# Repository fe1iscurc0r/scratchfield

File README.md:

# scratchfield — 实验田

[中文](README.md) · [English](README_en.md)

> 连接即正义，控制即毁灭。
> 集成地狱不是事故，是特色。我们把别人的灵感拔下来，授粉进自己的土壤，长成自己的东西。
> 我们不套壳——每个组件都带融合报告，来源、许可、改动点、验收，白纸黑字。

**scratchfield**（实验田）——以**授粉（Pollination）**为方法论的集成工程展示面 + 插件商城。活跃开发在私有工作仓进行，本仓是公开展示面，按里程碑快照更新。**当前快照：2026-10-07。**

## 这是什么

一句话：**把上游好想法「授粉」进自家系统，长成自己的东西。**

授粉不是 fork 粘贴，是"拆解 → 改造 → 集成 → 留下报告"。每个授粉组件都登记来源、许可、改造点、验收结果，许可账本见 `github_haul/FUSION-LOG-2026-08-16.md` 与 [NOTICE（第三方版权声明全集）](NOTICE)。

### 自家核心资产（本仓展示的主菜）

- **工具总线**（`mcpserver/`）——MCP 适配层，统一注册 / 调度 / 鉴权。自研，含多领域工具封装与 agent-manifest 契约。
- **射频大脑**（`mcpserver/rf_brain/`）——协议无关的射频解调链。自研：OOK 解码器家族（Acurite/LaCrosse/PWM/PPM/Manchester）、DSP 滤波链、dcp 二进制帧、哨兵桥入库。
- **无线电套件 radio_suite**——FT8/WSPR/SSTV/NOAA APT 解码、SDR 频谱面板、APRS iGate、IC-705 CI-V 控制。独立组件走总线接入本体。
- **哨兵网格固件**（`firmware/`）——ESP32-S3 + SX1278 边缘频谱哨兵，433MHz 传感器信号从天线到记忆的完整链路。自研。
- **科研工作台**——ELN 实验记录、文献库、材料数据工具台（TGA/DSC/XRD）、材料性能预测管线；领域包机制（`domains/`）支撑多学科扩展。
- **授粉插件商城**（`plugins/`）——所有授粉改造过的组件统一登记，自由添加、即插即用。
- **记忆钩子**（`hooks/`）——事实索引 / 矛盾检出 / supersedes 边。自研。
- **NEKO 集成体**（`NEKO/`）——**旗舰授粉案例**：以 Apache-2.0 上游 NEKO 桌宠为身体层（Live2D/TTS/ASR/视觉），自研集成层（启动 wrapper、provider overlay、注入路由、灵魂桥）将其接入自家人格内核（记忆 / RAG / 决策）与 Hermes 生态。

### 近期亮点（2026-10 快照）

- **巨石治理收官**——agentserver 主入口 3096 行拆为 30 行薄入口 + 11 子模块；前端 SkillView/App/ForumSidebarRight 三大巨石组件分步拆解，App.vue 转向 composable 架构并附状态依赖图
- **Agent 安全防线**——5 篇前沿攻击论文（间接注入/技能组合失控/跨租户干扰）转化为威胁模型清单，工具总线新增风险等级注解与任务级调用链留痕
- **RF-Agent 频谱调度设计**——参考层级语言-Agent 频谱感知架构，为 IC-705/RTL-SDR 工作流设计三层调度（指令理解→任务规划→设备执行），设计稿先行
- **材料线对口授粉**——sparse AFM 跨尺度力学重建、纳米颗粒分散度过程链优化两篇方法论落地为调研笔记，直连木质素 NPs→水凝胶研究主线
- **授粉轮 35 期持续产出**——热分析动力学、EIS、糖链与聚合物拓扑、GNSS 定位安全等十轮方法论报告入库
- **配置收口与配置即文档**——apiserver 环境变量统一进 config.py + .env.example 全量补齐
- **一键体检**——`scripts/doctor.py` 应用层自检 + `doctor_env.py` 环境自检，装到哪一步坏了一眼可见

### 身份声明

- 本仓是**授粉实验田**，不是任何上游的套壳。底层引擎（NagaAgent、NEKO、llama.cpp 等 Apache/MIT 组件）只是技术栈的一部分，列于各组件致谢；自家产出是集成层、工具总线、射频/固件、授粉插件。
- 类比：Chrome 基于 Chromium，Firefox 基于 Gecko——引擎是引擎，品牌是品牌。我们卖的是"把上游消化成自己的"这个能力。
- 每个授粉条目的来源与许可边界见 FUSION-LOG 与各插件条目，法律与道义都讲得清。

## 授粉是什么

授粉 = 上游灵感 → 拆解 → 改造 → 集成。不是 fork 粘贴，而是把「能长进我们系统的那部分」移植进来，留下完整的授粉报告（来源 / 许可 / 改造点 / 验收）。许可账本见 `github_haul/FUSION-LOG-2026-08-16.md`。

## 目录

| 路径 | 内容 |
|------|------|
| `mcpserver/` | 工具总线（自研，含 rf_brain 射频大脑） |
| `apiserver/` | FastAPI 主后端（ELN/文献/数据工具/人格/记忆） |
| `frontend/` | Vue 3 桌面壳（频谱面板/数据工具台/设置页） |
| `domains/` | 领域包（materials/law，可扩展第三领域） |
| `firmware/` | ESP32 固件（哨兵网格，自研） |
| `plugins/` | 授粉插件商城（注册表 + 添加/安装脚本） |
| `hooks/` | 记忆钩子（事实索引/矛盾检出，自研） |
| `NEKO/` | NEKO 集成体（旗舰授粉案例：上游身体 + 自研集成层） |
| `skills/` | 190+ 技能库（研究/无线电解耦） |
| `docs/` | 架构 / 授粉报告 / SPEC |
| `github_haul/` | 扫货索引 + 许可账本 |
| `scripts/` | 工具脚本（插件添加/安装/自检等） |

## 快速开始

**最短路径见 [QUICKSTART.md](QUICKSTART.md)**（普通用户下 exe / 开发者源码路线 ≤10 步）。
环境细节与已知坑见 **[环境依赖清单（Windows 装机指南）](docs/环境依赖清单-Windows装机-2026-09-27.md)**——Python 严格 3.12.x、只用 npm、uv 不裸 pip，写死的版本要求都在里面。

集成体启动步骤见 `NEKO/N.E.K.O/README.MD`。插件商城使用见 `plugins/README.md`。

```bash
# 环境体检（装之前）
python doctor_env.py
# 查看商城
cat plugins/index.json
# 装一个插件到运行时
./scripts/plugin-install.sh <plugin-id>
# 应用层体检（装之后）
python scripts/doctor.py --quick
```

## 项目小传

本仓的完整来历、方法论与演进史，见 [STORY.md](STORY.md)——从一张私有工作台，到把几十个开源项目的灵感授粉成自有体系的两年实验记录。

## 许可

AGPL-3.0（见 LICENSE）。闭源商用需单独授权。**上游组件的完整版权与许可声明见 [NOTICE](NOTICE)**；各插件条目与 FUSION-LOG 亦有分账记录。

---

维护：fe1iscurc0r · 实验田，快照更新（2026-10-07）

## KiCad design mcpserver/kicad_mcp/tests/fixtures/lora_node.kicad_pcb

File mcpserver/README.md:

# mcpserver — 工具总线（使用+维护指南）

这是全系统的"能力插座"：所有工具（MCP）在这里注册、调度。FastAPI 入口 + 三表注册中心 + 统一调度。

## 你能用的工具（使用者视角）

| 模块 | 做什么 | 怎么调 |
|------|--------|--------|
| material_science | 科研（matchat 桥/生物预测/数据集构建） | Lumo 里直接说需求 |
| rf_brain | 射频解调链（建设中） | 等真机 |
| agent_game_guide | 游戏攻略 | 问陆墨 |
| agent_open_launcher | 打开应用 | 说"打开XX" |
| agent_screen_vision | 屏幕视觉 | 截图分析 |
| agent_weather_time | 天气时间 | 问"天气" |
| tts_api | 语音合成 | 桌宠说话 |

## 外部 MCP 服务（可启用，默认关闭）

- toolbox-postgres（数据库）、swarmvault（LLM Wiki/RAG）、mentedb（记忆引擎）、arcrift（编程跨会话记忆）、apify（网页抓取）
- 启用：改 `external_services.example.json` → 合入 `~/.mcporter/config.json`，置 `false` 生效

## 架构三句话

1. **三表注册**：MCP_REGISTRY（服务池）+ MANIFEST_CACHE（manifest 缓存）+ _ADAPTER_CAPABILITIES（adapter 能力）
2. **统一调度**：`POST /schedule` → MCPManager.unified_call() 路由
3. **适配层**：adapters/ 只做凭证 fail-fast + sys.path 注入 + 暴露函数，业务在 vendor 代码里

## 加新工具（开发者）

1. `mcpserver/<name>/` 建目录 + `agent-manifest.json`（name/description/tools/entryPoint，支持 A/B/C/D 四种格式）
2. 或走 mcporter_bridge 外部服务
3. 注册冲突自动检测（WARNING 不阻断）

## 测试与规范

```bash
python -m pytest tests/test_mcp_adapters.py -x   # MCP 适配层
python -m ruff check .                            # 格式化检查
```

- 模块加载白名单：只允许 `mcpserver.` / `vendor.` 前缀
- Adapter 健康检查不过自动跳过，不让全局启动失败
- API Key 走环境变量，不硬编码绝对路径

## 企业级参考（规模化时抄）

- `mcp-gateway-registry`（MIT）：OAuth/Keycloak 集中鉴权、动态工具发现、安全扫描
- `arcade-mcp`（MIT）：Python MCP 框架，声明式 OAuth（GitHub scopes 等 22 provider）

---
*维护：实验田维护者 2026-08-22*

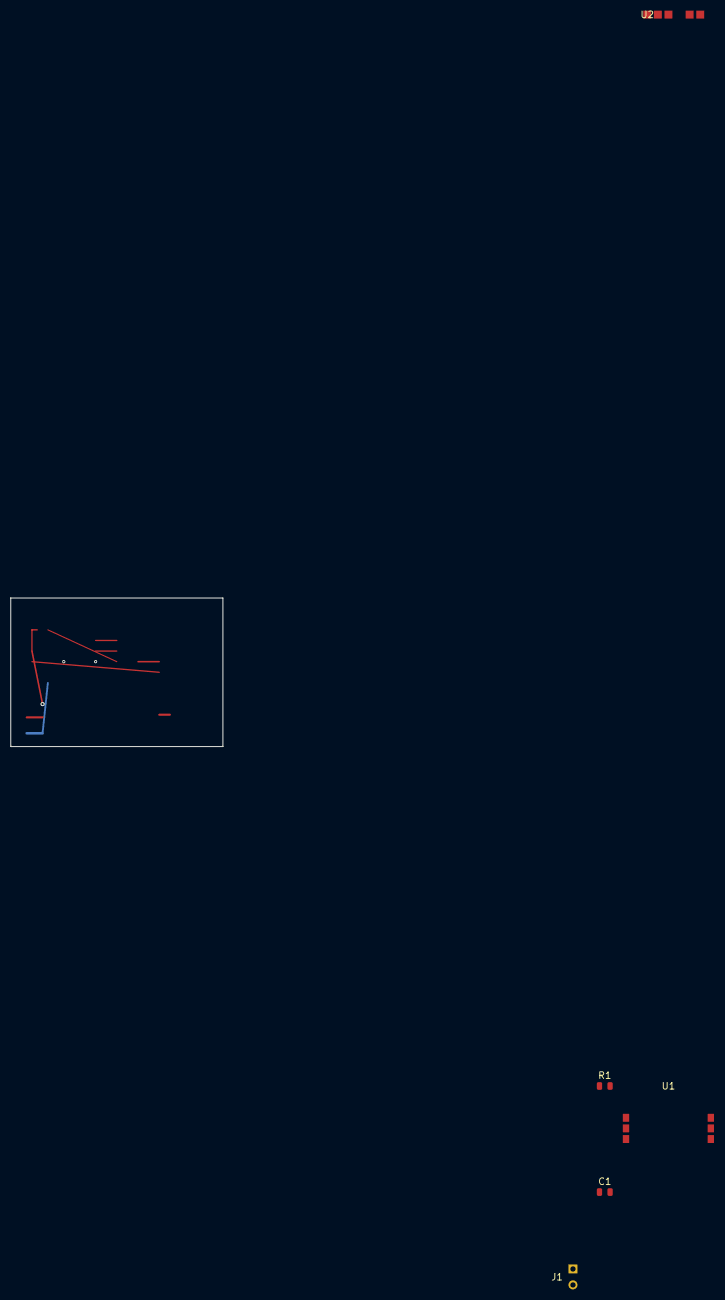
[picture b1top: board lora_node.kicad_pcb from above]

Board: 4 copper layers, 40.0 x 28.0 mm, 5 parts (0 on the bottom side), 4 nets.

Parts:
C1: 100nF; C_0805_2012Metric
J1: BAT-2P; PinHeader_1x02_P2.54mm_Vertical
R1: 10k; R_0805_2012Metric
U1: ESP32-S3-WROOM-1
U2: Ra-01-SX1278; Ra-01

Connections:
+3V3: C1.1, R1.1, U1.2, U2.1
CS_LORA: R1.2, U1.6, U2.3
GND: C1.2, J1.2, U1.1, U2.5
SPI_SCK: U1.3, U2.2
